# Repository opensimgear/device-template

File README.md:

# OpenSimGear device template

## Development status and disclaimer

This project is heavily under development and is not ready for use. Use it entirely at your own risk. To the fullest extent permitted by applicable law, the authors and contributors disclaim all liability for any damage, loss, or other issues arising from its use.

Start a new device with C firmware, electronics and mechanical designs in one repository. The **STM32G0B1CBT6 v0.1.0** starter provides **eight analogue inputs, 24 digital lines and optional 16-input I²C expansion boards**. A build-time profile supplies factory defaults; validated runtime configuration selects and calibrates the controls a particular device uses.

## What is implemented

- Configurable buttons, maintained contacts, analogue axes, eight-way hats, rotary encoders and three-position selectors. Unused controls are omitted from the HID descriptor and report.
- `example`, three-command `shifter`, `expanded`, single-button `master_caution` `radio_panel` and CDC-only `output_only` factory profiles; runtime drafts cover every control kind, channel mapping, axis calibration/inversion/deadzone, expansion masks and Unicode controller names. Validation rejects overlapping pins and oversized HID reports.
- One bounded configuration writer, explicit Apply/Save/discard/reset, a separate interrupted-write-safe settings journal, and direct USB descriptor replacement while detached. Cockpit accesses the same runtime core through the matching gateway; the independent JSON device simulation runs this C implementation.
- Optional 3.3 V TCA9555 input boards on I²C, with missing-board diagnostics and recovery that prevents held momentary contacts from generating a new press.
- Composite USB HID + CDC serial, unique serial number from the MCU's 96-bit UID.
- Serial `hello`, `info`, `inputs`, LED control and CAN status diagnostics.
- Device-advertised volatile actions with typed parameters, catalogue revisions and state readback. Cockpit controls the current board's monochrome status LED and the native simulator's RGB LED 1/boolean LED 2 through the same action registry and gateway route, including disabled HID controllers and direct USB ownership.
- Independent mapped-button/encoder transition capture with a 64-record volatile log, 16-record pages, held-state baselines and explicit stream/gap errors. Short debounced presses remain readable while HID is disabled or direct USB owns input. The Master Caution simulator uses the board LED action contract. Radio observations add maintained/selector metadata and independently calibrated axes with availability flags.
- Bounded character-display ports with declared columns, rows and ASCII/UTF-8 scalar-cell encoding, typed text setters and callback readback. The native radio supplies 7-cell frequency, 2-cell preset and 16-cell text ports through production firmware. The starter has no fitted display and advertises only its actual LED.
- Cyphal/CAN device with automatic node-ID selection, standard Heartbeat/GetInfo, profile discovery and input delivery through the STM32 gateway; direct USB ownership and completion-acknowledged encoder events.
- Shared profile validation, HID descriptor generation, debouncing, axis scaling, hat decoding, bounded encoder events, TCA9555 acquisition and line handling in [firmware-common](https://github.com/opensimgear/firmware-common), with pinned dependencies.
- KiCad schematic, exact-part BOM and local libraries, with separate four-layer production and two-layer Makera Z1 layouts. One current circuit is maintained at PCB version 0.1.0; [versions stay fixed until launch](electronics/VERSIONING.md).

**Status on 2026-10-14:** all six factory profiles cross-build and seventeen native suites pass with address/undefined-behavior sanitizers, including independent calibrated axes, bounded display callbacks, panel events, advertised actions, runtime configuration, actual dynamic USB descriptor callbacks, Unicode names, CAN delivery and interrupted settings/boot-journal writes. Cross-firmware tests connect actual acquisition/client code to the [device-gateway](https://github.com/opensimgear/device-gateway) discovery, registry and USB completion logic. Production schematic ERC, PCB DRC and schematic/PCB parity pass with zero violations or missing connections. These are software and CAD checks; no STM32 board has been physically validated. Runtime input configuration and saved calibration are implemented in portable code and the STM32 adapter. Gateway discovery now automatically enables new compatible identities in persistent descriptor order, with logical CAN routes 1–32. Explicitly disabled devices remain configurable without a gateway HID collection; re-enabling appends them. Matching gateway/device helpers are required for routes above ten. Implementation and qualification work is tracked in the [GitHub project](https://github.com/orgs/opensimgear/projects/2).

## Start here

- [Run native devices from JSON](simulation/README.md)
- [Firmware build, flash and console instructions](firmware/README.md)
- [CAN integration, ownership and firmware validation](firmware/CAN_BRINGUP.md)
- [Input examples, HID mapping and control wiring](firmware/profiles/README.md)
- [Starter board and pinout](electronics/boards/starter/0.1.0/README.md)
- [Optional 16-input expansion board wiring](electronics/expansion/tca9555/README.md)
- [Fabrication construction and home-milling plan](electronics/boards/starter/0.1.0/FABRICATION.md)
- [Validation record](electronics/boards/starter/0.1.0/VALIDATION.md)
- [Schematic PDF](electronics/boards/starter/0.1.0/review/schematic.pdf)
- [Front copper preview](electronics/boards/starter/0.1.0/review/pcb.svg)

## Run simulated devices

Start Cockpit normally and run the gateway from the [device-gateway simulation](https://github.com/opensimgear/device-gateway/tree/main/simulation). From this repository, start a separate terminal for each device:

```sh
python3 simulation/run.py --config simulation/configs/pedals.json
python3 simulation/run.py --config simulation/configs/button-panel.json
python3 simulation/run.py --config simulation/configs/shifter.json
python3 simulation/run.py --config simulation/configs/master-caution.json
python3 simulation/run.py --config simulation/configs/radio-panel.json
python3 simulation/run.py --config simulation/configs/output-only.json
```

Each JSON declares a unique identity, controller name and input arrays. `output-only.json` and `output-only-board-led.json` declare empty inputs with the same production RGB/boolean or fitted monochrome LED callbacks. They enroll without a HID controller and accept exclusive volatile endpoint leases with independent expiry/fallback. The gateway exposes the devices to Cockpit through its ordinary protocol. The first launch initializes pinned dependencies and builds into this repository’s `.simulation/`; saved configuration survives independent device, gateway and Cockpit restarts. See the [simulation guide](simulation/README.md) for JSON fields, input controls, state isolation and native tests.

Gateway and Cockpit E2E runners clone the components they require under their own `.e2e/` directories and initialize dependencies before building. This repository’s integration workflow checks out an immutable gateway runner commit with the same firmware-common pin, then supplies the current device source explicitly. Build commands do not invoke another repository’s E2E runner.

## Create a device

1. Select **Use this template** on GitHub. Replace the device overview and remove unused edition placeholders.
2. Keep common implementation in firmware-common; update its full commit pin deliberately.
3. Copy a firmware profile, assign its physical inputs and HID usages, and select it with `OSG_DEVICE_PROFILE`. The profile supplies factory defaults for USB descriptors, input reports and Cyphal capability announcements. Cockpit can configure the module through the matching gateway, including all input kinds and calibration; the module USB console also accepts `config <child-command>`. Explicit Apply detaches USB before publishing a changed descriptor, and Save persists settings. See the [runtime command contract](https://github.com/opensimgear/protocol/blob/main/serial/runtime-configuration.md).
4. Supply USB IDs you are authorized to use before flashing. No public OpenSimGear allocation is claimed.
5. Change the board target and electronics together, adapt the routing and complete the documented checks before fabrication.
6. Add mechanical designs under `hardware/variants/<edition>/<revision>` and maintain a compatibility table mapping mechanical revisions and PCB versions to compatible firmware targets.

## Layout

| Directory | Ownership |
| --- | --- |
| `simulation/` | Independent native device runtime, JSON examples, build/launch commands and tests |
| `firmware/` | Application, physical control profile, board target and build entry point |
| `electronics/boards/starter/0.1.0/` | Generic PCB/schematic, BOM, pinout and validation |
| `electronics/expansion/tca9555/` | Compatible optional input-board wiring and qualification contract |
| `hardware/variants/lite/` | Reserved Lite mechanical directory |
| `hardware/variants/pro/` | Reserved Pro mechanical directory |

Lite/Pro editions may share firmware and electronics. A material change alone does not require a new controller identity or copied firmware. Mechanical designs remain placeholders. Gateway electronics and firmware live in [device-gateway](https://github.com/opensimgear/device-gateway). Template updates do not automatically update repositories created from it.

## Licensing

Copyright © Ivan Gregurić Ortolan. All rights reserved for original OpenSimGear material while licensing is under review. The [temporary licensing policy](LICENSE) defines the current scope for firmware, electronics, mechanical designs and other original material. Creative external contributions are suspended during review; [CONTRIBUTING.md](CONTRIBUTING.md) explains the policy for factual bug reports and questions. Included KiCad library data retains its own [license](electronics/boards/starter/0.1.0/LICENSE-KICAD.md). Fetched firmware dependencies retain their upstream licenses; see [third-party notices](firmware/THIRD_PARTY.md).

## JLCPCB exports

From this repository root, run `sh tools/bundle-jlcpcb.sh` for the latest numeric board version, or `sh tools/bundle-jlcpcb.sh 0.1.0` for a specific version. Requires KiCad 10 (`kicad-cli`) and Python 3. The script generates a Gerber ZIP plus separate JLCPCB BOM/CPL CSVs in the workspace `.research/jlcpcb/` directory. Use `--output-dir path` to change the destination or `--smd-only` to omit through-hole assembly. See [tool usage](tools/README.md) and the board’s fabrication notes before ordering.

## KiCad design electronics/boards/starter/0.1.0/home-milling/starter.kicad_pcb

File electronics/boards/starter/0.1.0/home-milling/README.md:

# Home-milling device prototype

## Development status and disclaimer

This project is heavily under development and is not ready for use. Use it entirely at your own risk. To the fullest extent permitted by applicable law, the authors and contributors disclaim all liability for any damage, loss, or other issues arising from its use.

This is a separate two-layer bench layout of the canonical v0.1.0 circuit in the parent directory. It targets a Makera Z1 with the PCB toolkit and **unplated holes**. The additional area reserves accessible 1.80 mm wire lands for every MCU signal and the larger generic input banks. The assembled board is 105 × 125 mm; the routed blank is 110 × 125 mm including a removable 5 mm registration rail on its west side. USB and both powered-CAN sockets face the east edge. The nominal USB and RJ connector mouths align with the east PCB edge. Verify actual plug access, connector fit and strain clearance with purchased parts.

The layout keeps the original STM32G0B1CBT6 LQFP48, USB4105-GF-A, TCAN3413D and LM66100 component lands. Open signal runs use 0.30 mm tracks; local IC escapes, crowded routing lanes and USB use 0.20 mm. The final layout contains 4,586 mm of 0.30 mm copper and 1,395 mm of 0.20 mm copper; wider power routing is counted separately. Copper clearance is at least 0.20 mm. The editable stackup records two bare 35 µm copper faces and a nominal 1.53 mm FR4 core for a 1.60 mm laminate; actual copper/core thickness and dielectric properties must be measured or supplied by the laminate vendor. The nominal epsilon/loss values are metadata assumptions, not an impedance design. The 12 V pass-through is 1.00 mm. BUCK_5V uses 0.4002–0.50 mm, SYS_5V uses 0.20–0.50 mm including a short regulator escape, USB_VBUS uses 0.20–0.30 mm, and +3V3 uses 0.20–0.30 mm. Narrow pin transitions and the eventual measured power budget require populated-board checks. Dimensions describe nominal copper, not a verified machining result.

## Generic input connections

This layout implements the same eight analogue channels, 24 digital lines and local I²C expansion interface as the canonical board. Each device wires only the controls enabled by its firmware profile. Unused control connections are omitted from the advertised controller profile.

| Header | Pin assignment |
| --- | --- |
| J5, J7–J13 | Eight axes A0–A7; pin 1 +3V3, pin 2 signal, pin 3 GND |
| J14 | Pins 1–6 D0–D5; pin 7 GND |
| J15 | Pins 1–6 D6–D11; pin 7 GND |
| J16 | Pins 1–6 D12–D17; pin 7 GND |
| J17 | Pins 1–6 D18–D23; pin 7 GND |
| J18 | Pin 1 +3V3, pin 2 SDA, pin 3 SCL, pin 4 GND |

Axes use the canonical per-channel input resistor, filter capacitor and weak midpoint bias. Digital contact inputs have 10 kΩ pull-ups and are intended to close to GND. I²C is a short internal 3.3 V connection for optional 16-input boards, not an external cockpit bus. Do not apply 5 V or 12 V to analogue/digital inputs or use the USB/CAN supply pins as control inputs. See the [shared electrical design](../ELECTRICAL.md) and [pin allocation](../pin-allocation.json).

## Qualify the actual process first

Mill and populate the [qualification coupon](coupon/README.md) before this device. The USB and MCU footprints have 0.20 mm nominal gaps, leaving no process margin if the machine only just achieves that isolation. Test the cutter, board flatness, measured thickness, probing, opposite-face registration, isolation, pad adhesion and hand soldering with the actual laminate and purchased parts. Optional toolkit solder mask does not change the copper target or establish USB impedance.

The removable rail has two 2.00 mm NPTH registration holes, at board coordinates (77.5,64) and (77.5,181) mm. They are a layout starting point. Measure the actual fixture/dowel pins and adapt hole diameter and fit before generating CAM; the kit's pin diameter has not been established. Remove the rail at the user-drawing guide x=80 mm after both faces and drilling are complete. Mounting holes on the finished board remain separate.

## Unplated construction

Every electrical layer transition uses a **0.80 mm drilled hole with 1.80 mm copper lands**, joined by a wire soldered on both faces. These are represented by KiCad vias solely to model the completed hand-wired connection. The raw milled board has no conductive barrel. The [wire-join list](review/wire-joins.csv) records all **224** positions and nets. Complete and inspect every join before power-on. This assembled connectivity includes 1,701 copper track segments. The wire diameter and solder fillet must fit the 0.80 mm holes. Toolkit rivets are not assumed to fit: a rivet with 1.00 mm outside diameter does not fit this selected hole.

Long-leaded Evercom 5301-4P4C contacts, headers, buttons and the RECOM converter attach electrically on the **bottom face only**. Front track/zone keepouts around those component holes prevent a hidden need to solder under a connector or component body. Their front annuli are mechanically incidental and cannot bridge faces.

The USB4105 shell is different. Its nominal 0.95 mm stakes do not reach the back surface of 1.6 mm laminate. Solder its four shell lands from the **front**, making accessible fillets outside the case; the front shell ground must reach a verified ground wire join. Inspect fit, solder access and mechanical retention on the actual sample before committing a device. Back annuli do not turn short shell stakes into through leads. USB SMD contacts also solder on the front. C6–C9 (MCU decoupling) and C11 (USB power decoupling) are back-face SMD capacitors. C6–C9 sit directly beneath the MCU and connect to its accessible supply and ground wire joins; solder and inspect these back-face paths. Populate back-face parts only after both faces have been milled, drilled and inspected.

Retained drill/slot dimensions are distinct from the isolation cutter:

| Feature | Nominal hole/slot |
| --- | --- |
| Manual wire layer joins | 0.80 mm round |
| USB shell stakes | 0.60 × 1.70 and 0.60 × 1.40 mm slots |
| USB locating pegs | 0.65 mm round |
| Evercom 4P4C contacts / both locating pegs | 0.90 / 3.20 mm round |
| Samtec header leads | 1.02 mm round |
| Omron button leads | 1.10 mm round |
| RECOM converter leads | 1.00 mm round |
| Board mounting / rail registration | 3.20 / 2.00 mm round |

A 0.80 mm drill cannot produce the USB's 0.60 mm slots. Plan suitable small-slot tooling/CAM and inspect actual component fit. Do not enlarge connector slots or locating holes just to use one tool. Electrical holes here are unplated despite the canonical footprints' commercial plated-hole descriptions; the parent footprint/source review explains the nominal manufacturer geometry.

## Electrical and USB limits

This is a bench prototype, with a two-layer ground arrangement and manually soldered connections. It is **not** the 90 Ω controlled-impedance fabrication layout. USB leaves the MCU through accessible soldered-wire joins and continues on the back before returning to the front protection/connector routing. Neither this two-layer geometry, its extra wire transitions nor successful enumeration qualifies USB signal integrity; enumeration and signal quality require bench testing with the actual assembled prototype. Use the parent's JLCPCB four-layer layout and specified impedance process for that review.

The exact CAN jack is Evercom 5301-4P4C (LCSC C3097715), with an 11.10 × 18.05 × 11.45 mm body and a nose 14.25 mm from its footprint origin. Both 3.20 mm locating holes retain the independently checked drawing dimensions. Pin 1 is BUS_12V, pin 2 CAN_H, pin 3 CAN_L and pin 4 GND; both jacks are parallel connections to one linear bus.

The circuit and firmware pin mapping are shared with the canonical version: USB direct operation, two CAN pass-through connectors, 12 V alongside CAN, local protection/regulation and USB/bus power selection. The RJ sockets are powered CAN, not telephone or Ethernet ports. v0.1.0 firmware implements Cyphal/CAN discovery, gateway input delivery and direct USB ownership; see [CAN integration](../../../../../firmware/CAN_BRINGUP.md). Software tests and this PCB review do not establish physical hot-plug, ownership handover or USB/CAN behavior. Perform continuity, shorts, power-rail and supply handover checks before connecting a PC or CAN chain.

## Shared circuit and source refresh

Run `python3 regenerate_schematics.py` from this directory to regenerate both home schematic files from the parent v0.1.0 sources. The generator modifies only symbol Footprint properties using `source-footprints.json`; all references, part values, net names and circuit connectivity remain shared. HomeMilling footprint variants retain the exact component land/drill dimensions. The board arrangement and wire-via rules are specific to this prototype. The [parent purchasing BOM](../bom.csv) identifies the same components; its footprint column describes the production layout. Use the HomeMilling variants here for this board, rather than changing the purchasing parts.

Review exports and native KiCad reports are under `review/`: [schematic PDF](review/schematic.pdf), [two-face routing PDF](review/routing.pdf), [front copper](review/front.png), [back copper](review/back.png), [ERC](review/erc.rpt) and [DRC](review/drc.rpt). The final source has zero ERC violations, zero all-track DRC violations, zero unconnected items and zero schematic parity issues. A separate construction audit models the long-lead component pads as bottom-only and the four short USB shell lands as front-only; it retains the documented wire joins and also finds zero unconnected items. Its intentional diagnostic pad transformations produce expected library/pad-type warnings, not changes to the deliverable PCB. See the [unplated connectivity record](review/UNPLATED-CONNECTIVITY.md), [independent construction review](review/CONSTRUCTION-AUDIT.md) and `audit_unplated.py` for the precise checks. No CNC toolpaths or machine-ready milling files are supplied. CAM must be generated against the qualified machine, fixture, cutter and measured laminate.

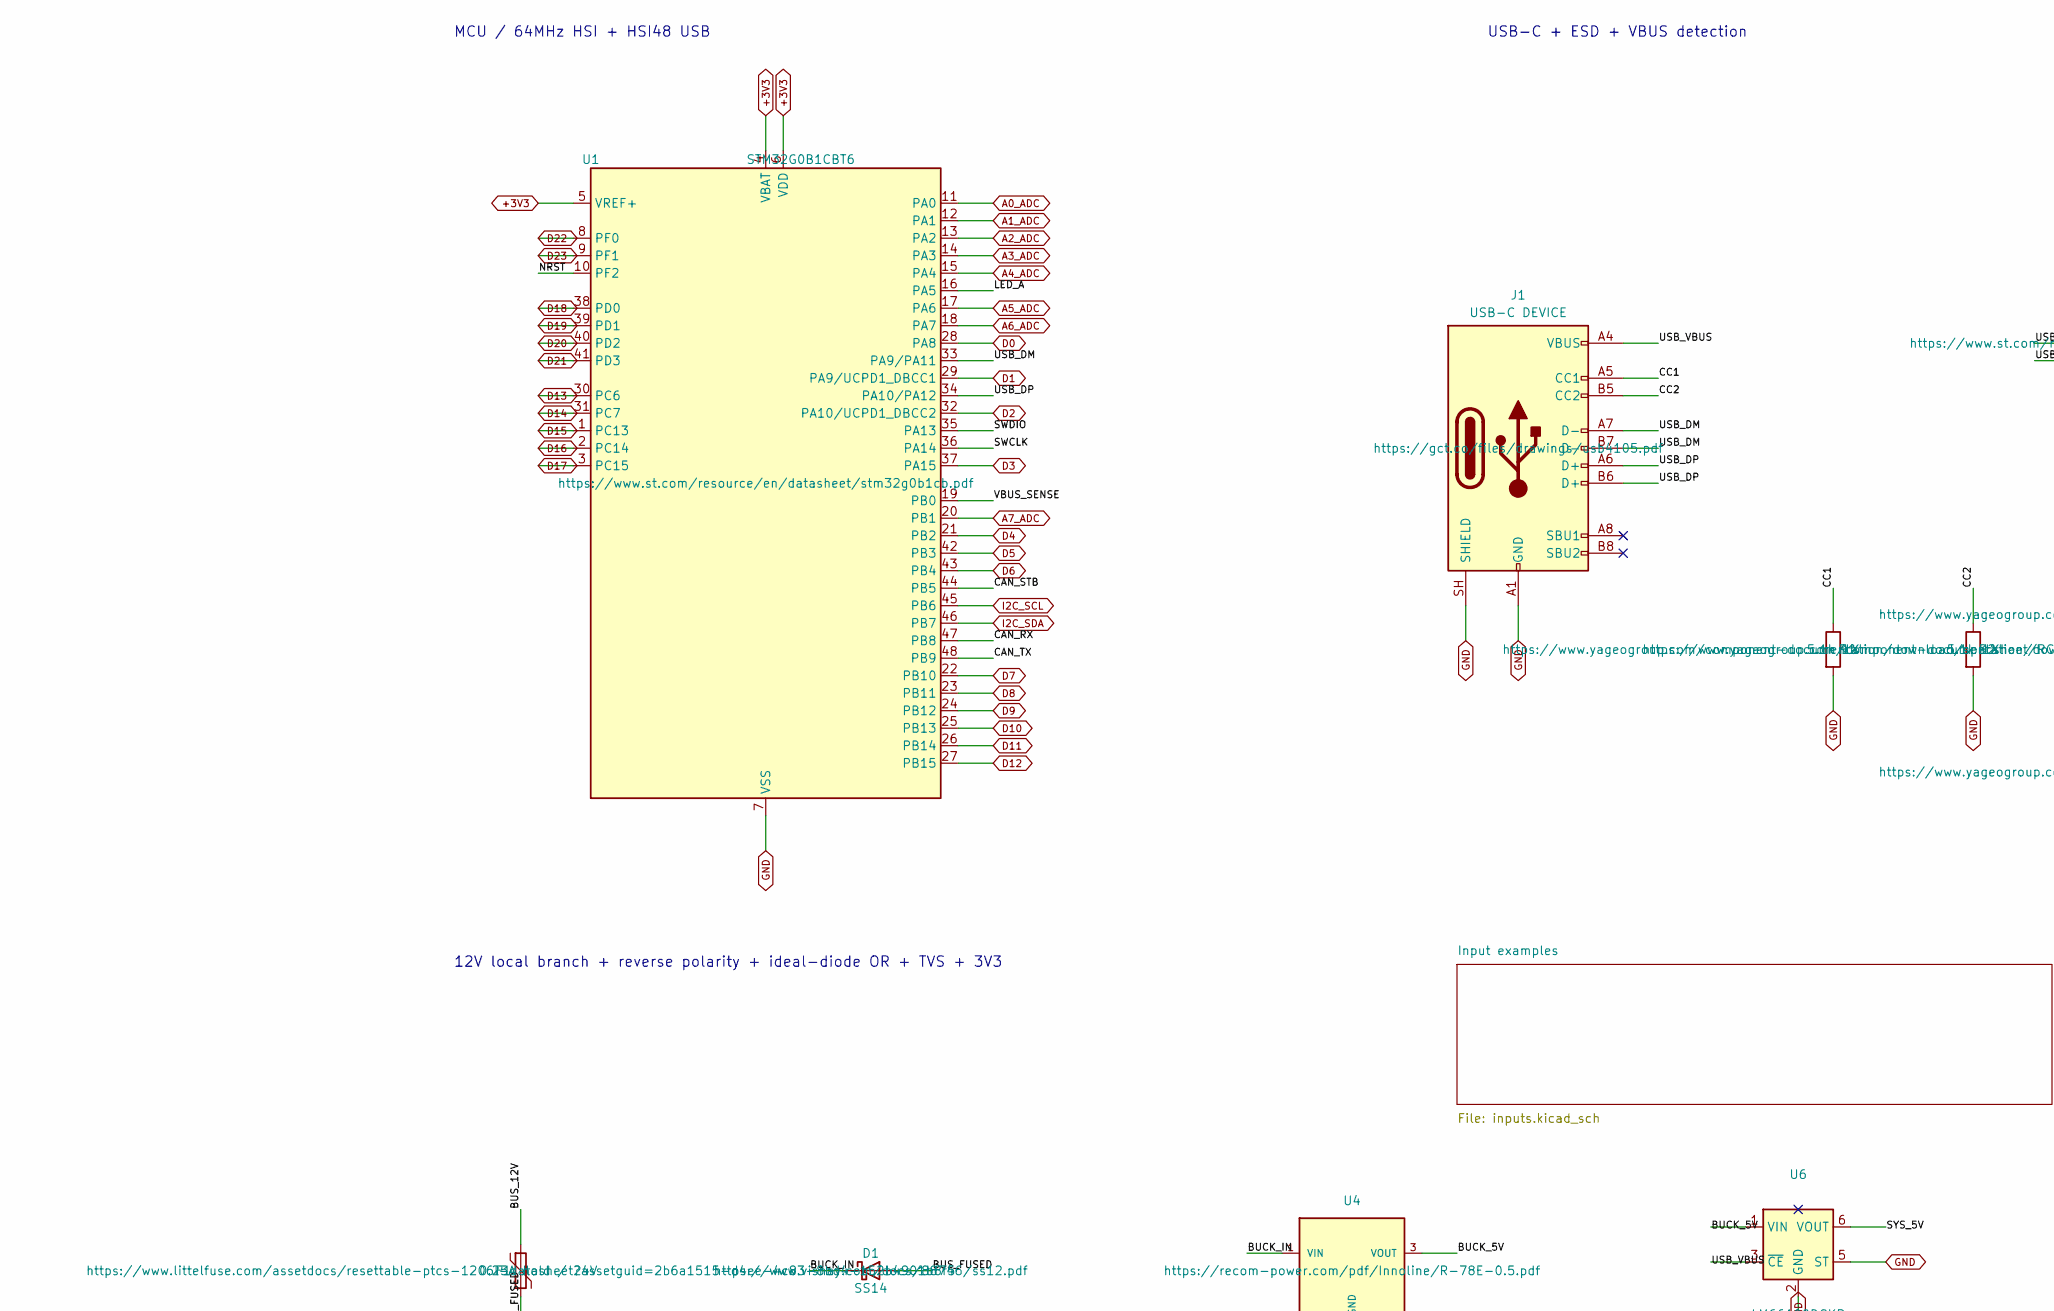
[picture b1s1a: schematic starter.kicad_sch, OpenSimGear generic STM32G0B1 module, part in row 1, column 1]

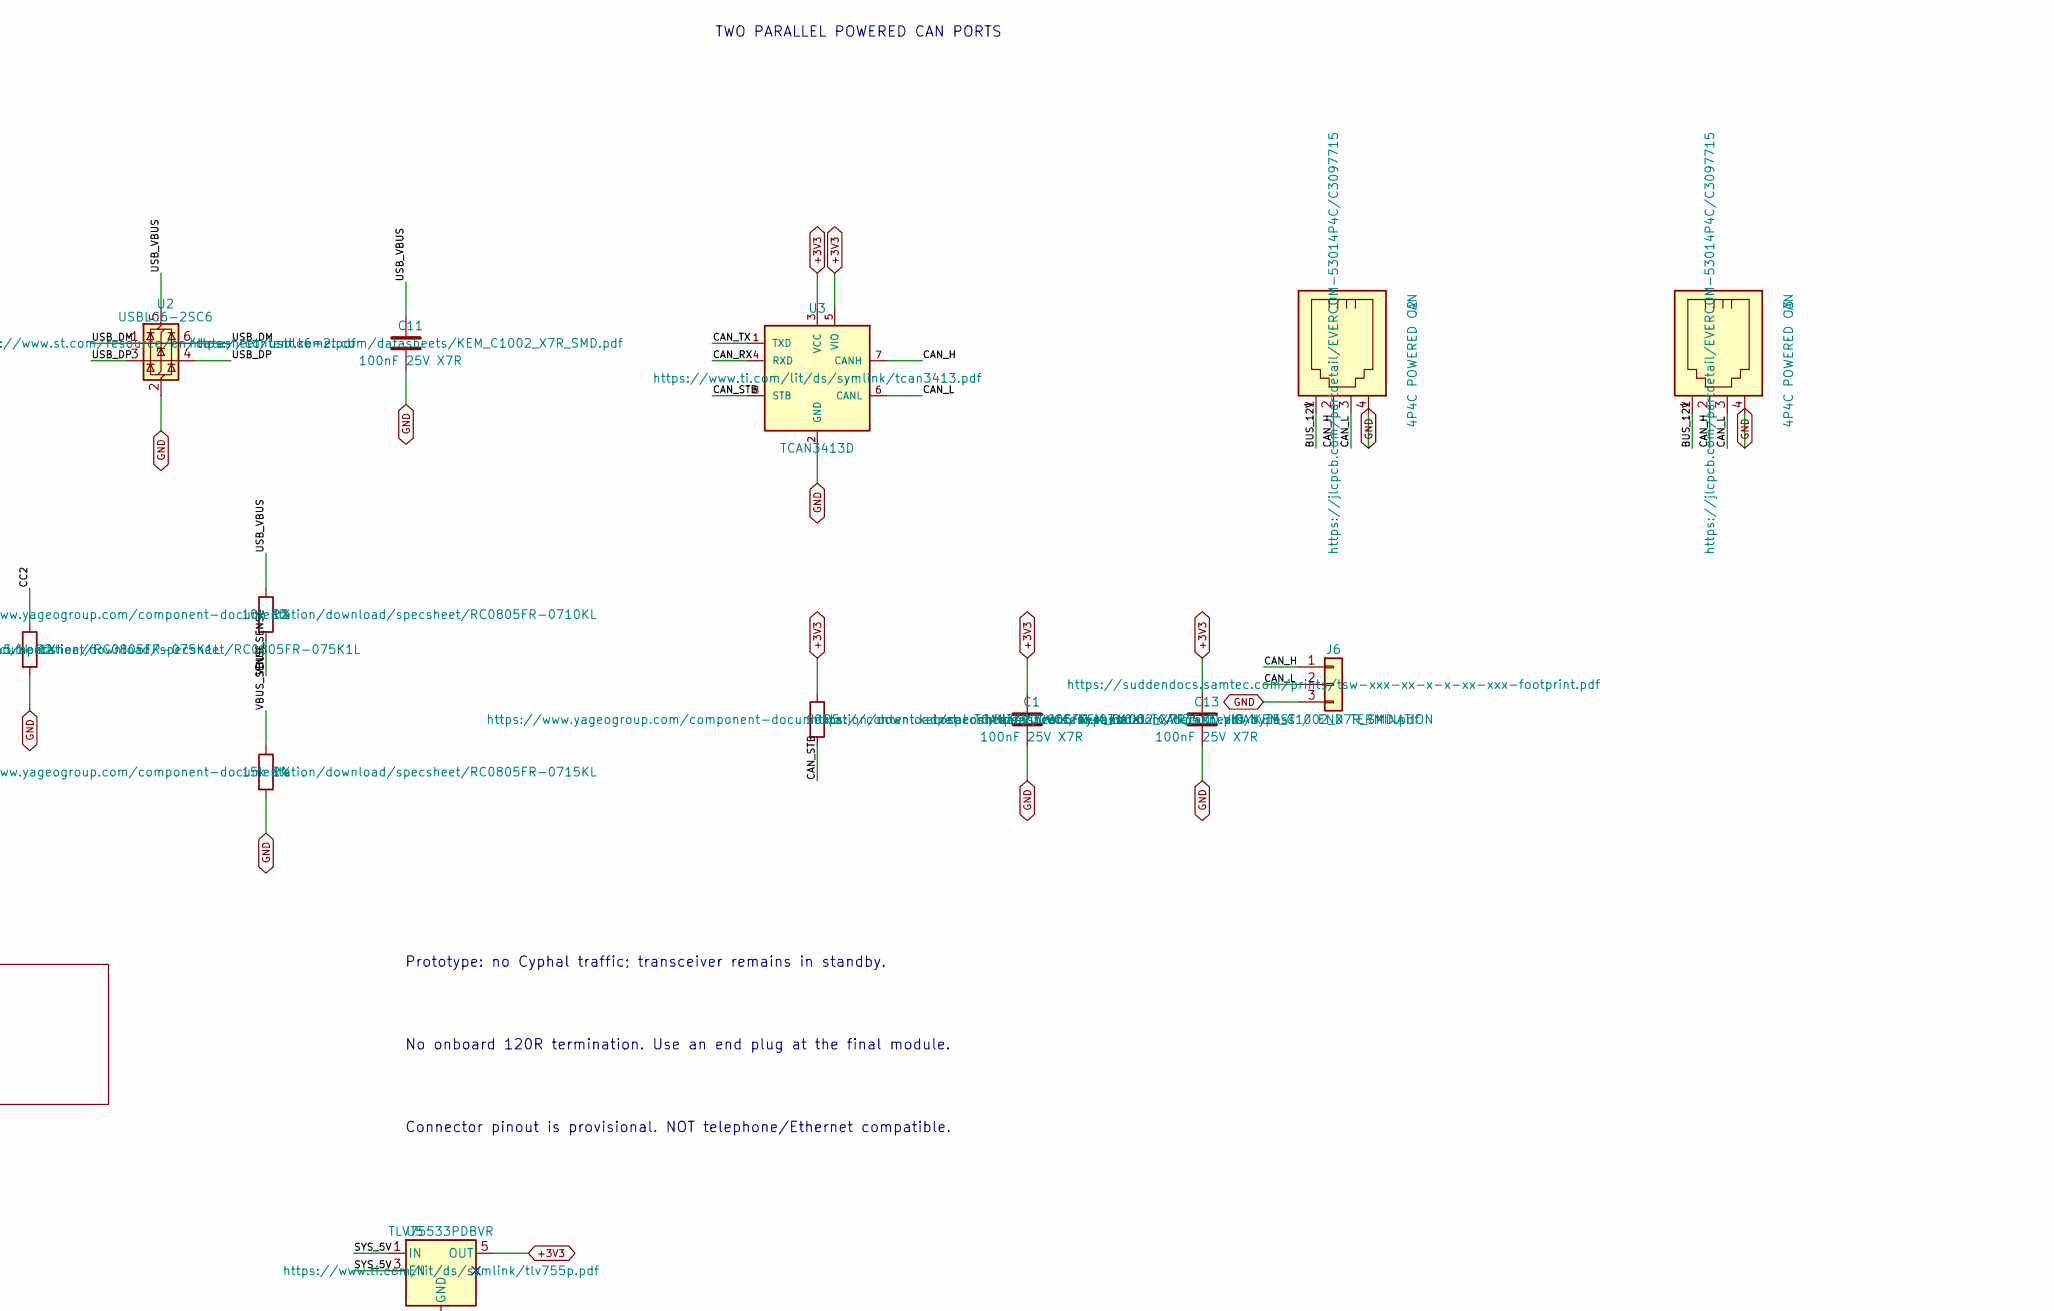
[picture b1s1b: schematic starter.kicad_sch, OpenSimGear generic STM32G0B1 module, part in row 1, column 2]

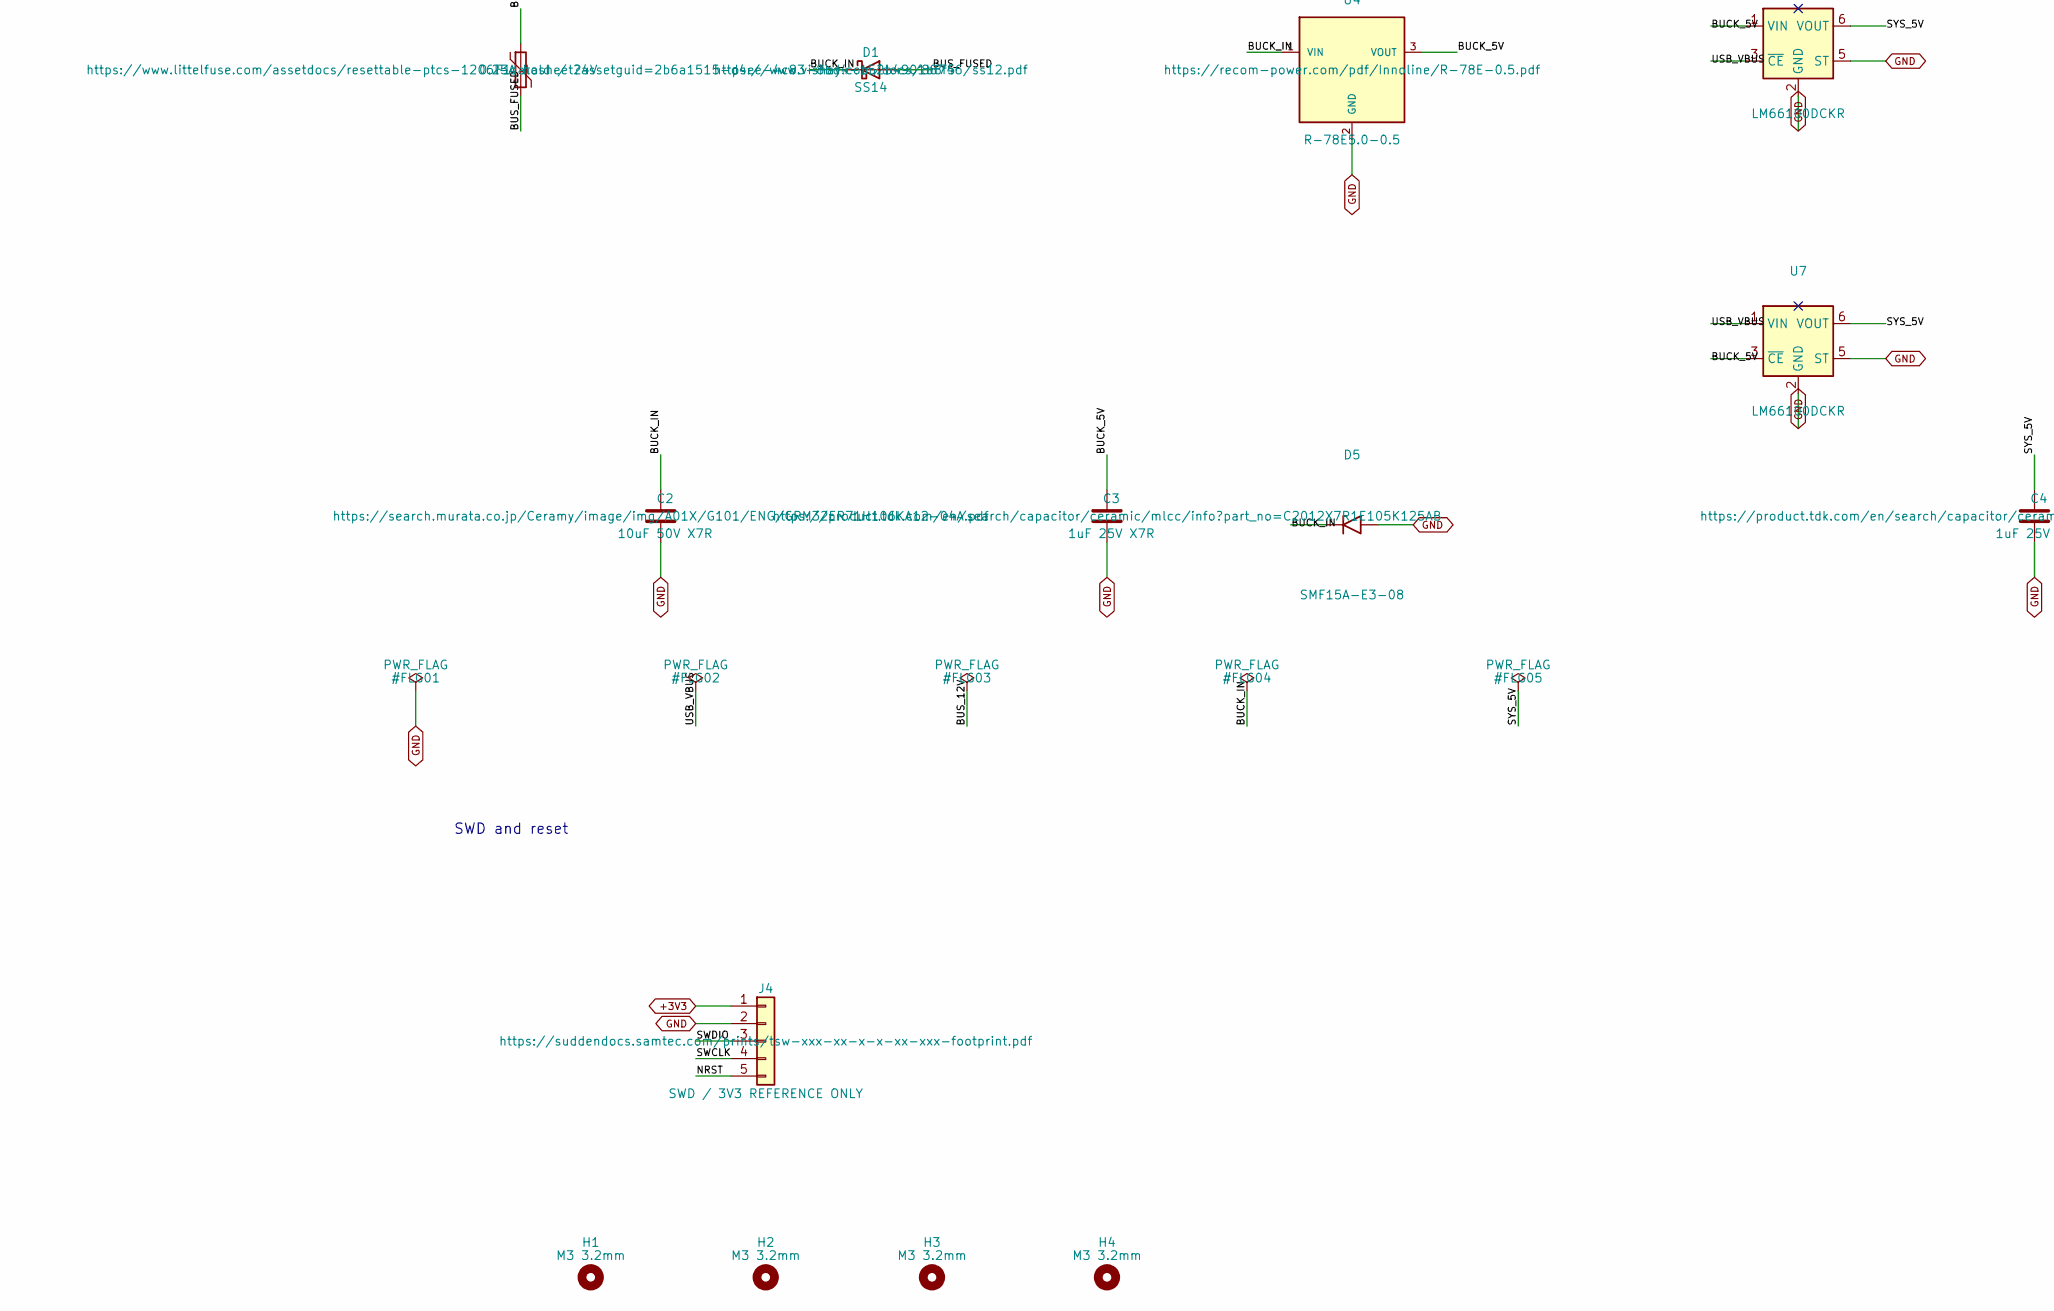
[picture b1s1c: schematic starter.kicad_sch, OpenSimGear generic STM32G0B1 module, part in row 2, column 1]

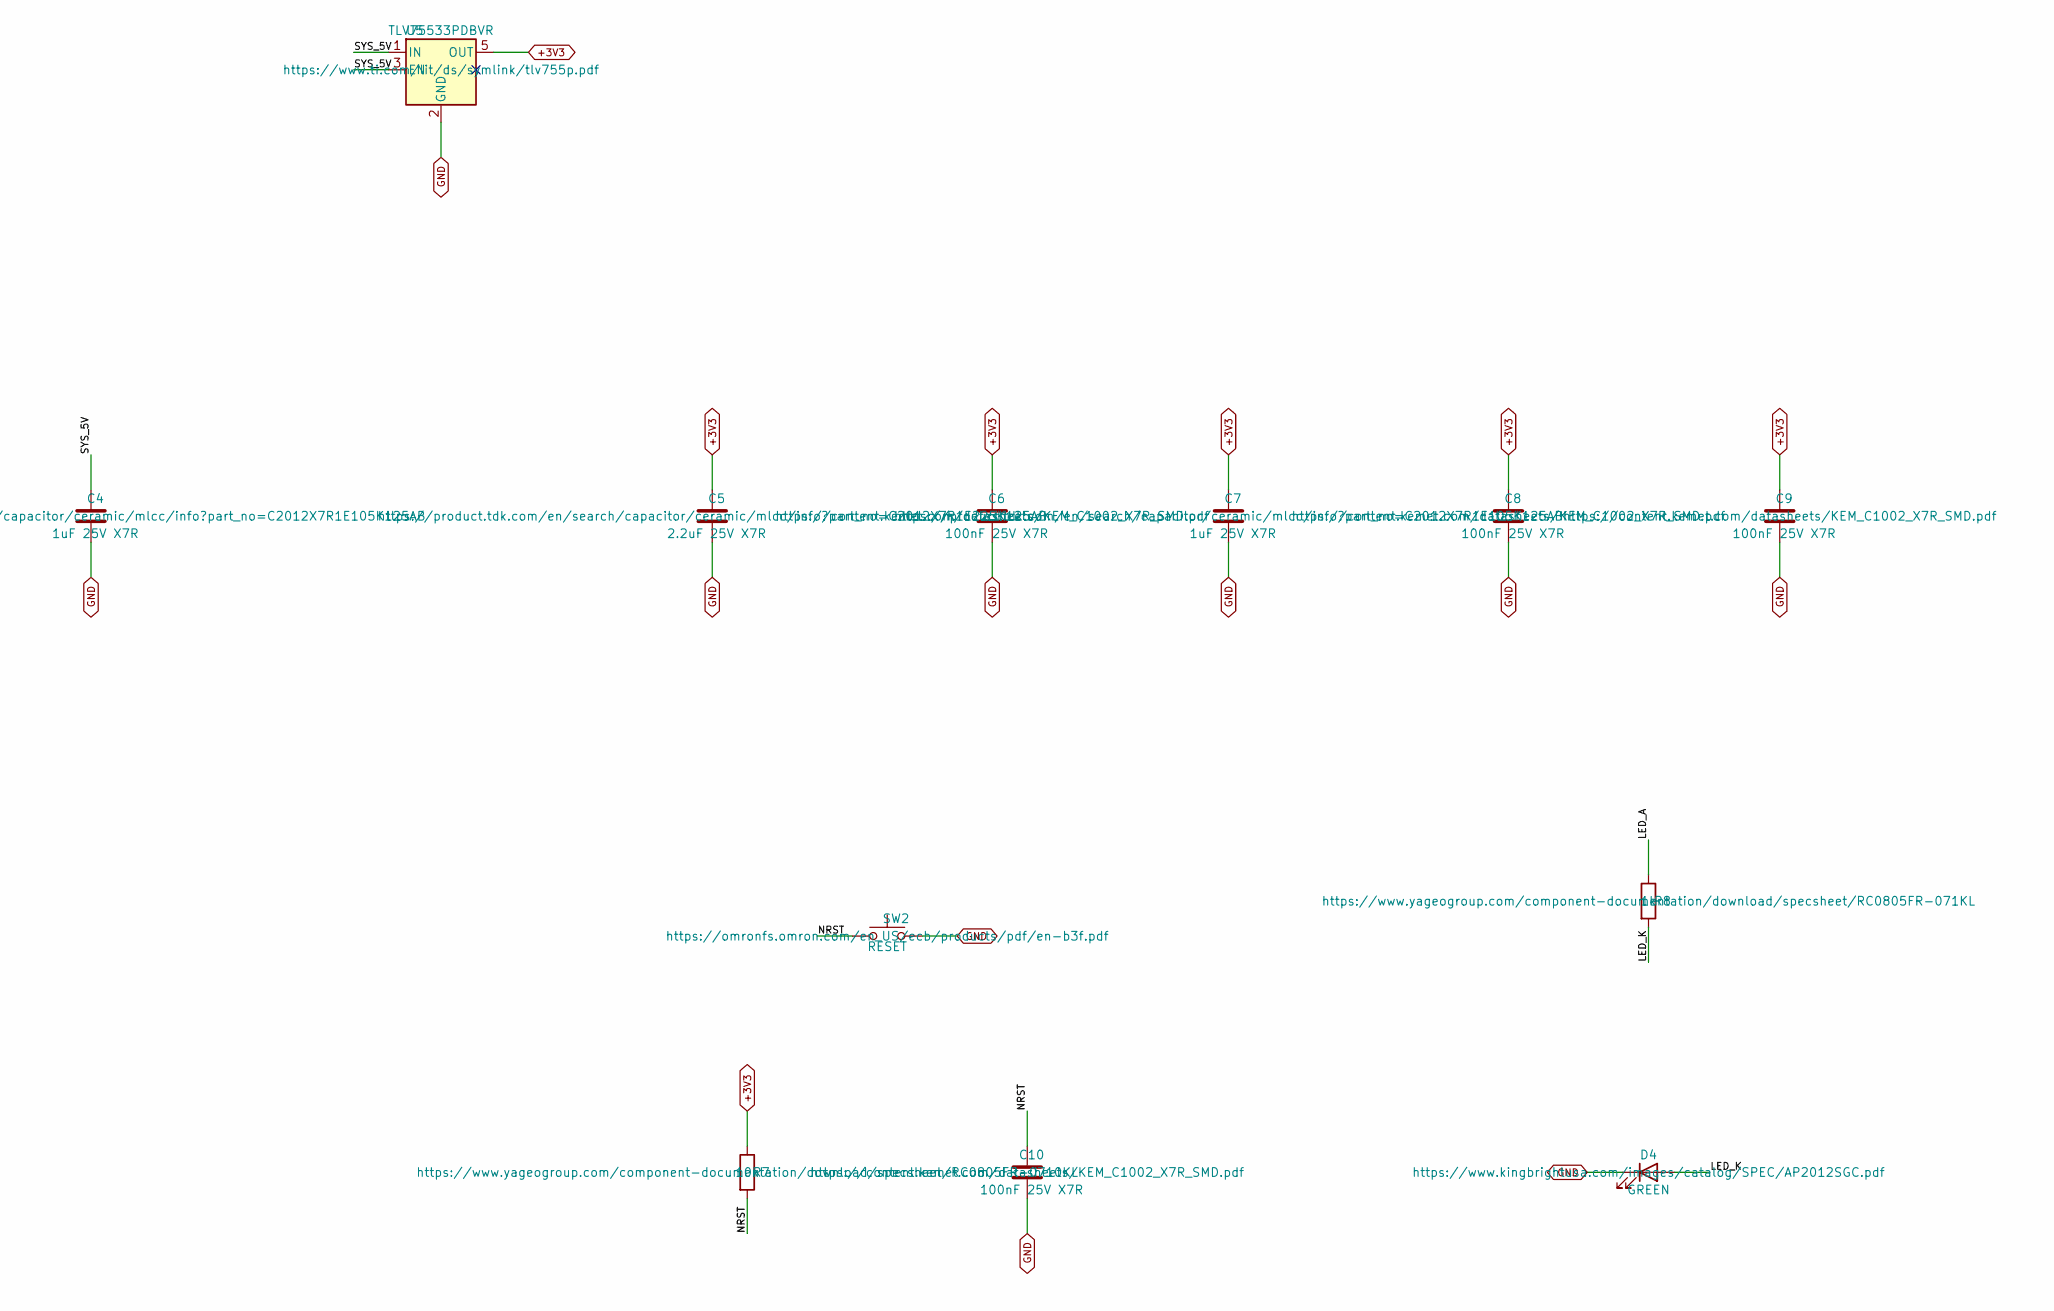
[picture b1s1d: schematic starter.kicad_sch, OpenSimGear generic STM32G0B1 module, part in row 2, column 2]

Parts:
C1: 100nF 25V X7R; C1_C_0805_2012Metric_HomeMilling; MPN C0805C104K3RACTU
C2: 10uF 50V X7R; C2_C_1210_3225Metric_HomeMilling; MPN GRM32ER71H106KA12L
C3: 1uF 25V X7R; C3_C_0805_2012Metric_HomeMilling; MPN C2012X7R1E105K125AB
C4: 1uF 25V X7R; C4_C_0805_2012Metric_HomeMilling; MPN C2012X7R1E105K125AB
C5: 2.2uF 25V X7R; C5_C_0805_2012Metric_HomeMilling; MPN C2012X7R1E225K125AB
C6: 100nF 25V X7R; C6_C_0805_2012Metric_HomeMilling; MPN C0805C104K3RACTU
C7: 1uF 25V X7R; C7_C_0805_2012Metric_HomeMilling; MPN C2012X7R1E105K125AB
C8: 100nF 25V X7R; C8_C_0805_2012Metric_HomeMilling; MPN C0805C104K3RACTU
C9: 100nF 25V X7R; C9_C_0805_2012Metric_HomeMilling; MPN C0805C104K3RACTU
C10: 100nF 25V X7R; C10_C_0805_2012Metric_HomeMilling; MPN C0805C104K3RACTU
C11: 100nF 25V X7R; C11_C_0805_2012Metric_HomeMilling; MPN C0805C104K3RACTU
C13: 100nF 25V X7R; C13_C_0805_2012Metric_HomeMilling; MPN C0805C104K3RACTU
D1: SS14; D1_D_SMA_HomeMilling; MPN SS14-E3/61T
D4: GREEN; D4_LED_Kingbright_AP2012SGC_0805_HomeMilling; MPN AP2012SGC
D5: SMF15A-E3-08; D5_D_SMF_HomeMilling; MPN SMF15A-E3-08
F1: 0.25A hold / 24V; F1_Fuse_Littelfuse_1206L025-24YR_HomeMilling; MPN 1206L025/24YR
H1: M3 3.2mm; H1_MountingHole_3.2mm_M3_HomeMilling
H2: M3 3.2mm; H2_MountingHole_3.2mm_M3_HomeMilling
H3: M3 3.2mm; H3_MountingHole_3.2mm_M3_HomeMilling
H4: M3 3.2mm; H4_MountingHole_3.2mm_M3_HomeMilling
J1: USB-C DEVICE; J1_USB_C_Receptacle_GCT_USB4105-xx-A_16P_TopMnt_Horizontal_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; MPN USB4105-GF-A
J2: 4P4C POWERED CAN; J2_RJ4P4C_Evercom_5301-4P4C_Horizontal_HomeMilling; MPN 5301-4P4C
J3: 4P4C POWERED CAN; J3_RJ4P4C_Evercom_5301-4P4C_Horizontal_HomeMilling; MPN 5301-4P4C
J4: SWD / 3V3 REFERENCE ONLY; J4_PinHeader_Samtec_TSW-105-07-L-S_P2.54mm_Vertical_HomeMil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; MPN TSW-105-07-L-S
J6: CAN TEST / END TERMINATION; J6_PinHeader_Samtec_TSW-103-07-L-S_P2.54mm_Vertical_HomeMil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; MPN TSW-103-07-L-S
R1: 5.1k 1%; R1_R_0805_2012Metric_HomeMilling; MPN RC0805FR-075K1L
R2: 5.1k 1%; R2_R_0805_2012Metric_HomeMilling; MPN RC0805FR-075K1L
R3: 10k 1%; R3_R_0805_2012Metric_HomeMilling; MPN RC0805FR-0710KL
R4: 15k 1%; R4_R_0805_2012Metric_HomeMilling; MPN RC0805FR-0715KL
R5: 10k; R5_R_0805_2012Metric_HomeMilling; MPN RC0805FR-0710KL
R7: 10k; R7_R_0805_2012Metric_HomeMilling; MPN RC0805FR-0710KL
R8: 1k; R8_R_0805_2012Metric_HomeMilling; MPN RC0805FR-071KL
SW2: RESET; SW2_SW_PUSH_6mm_H4.3mm_HomeMilling; MPN B3F-1002-G
U1: STM32G0B1CBT6; U1_LQFP-48_7x7mm_P0.5mm_HomeMilling; MPN STM32G0B1CBT6
U2: USBLC6-2SC6; U2_SOT-23-6_HomeMilling; MPN USBLC6-2SC6
U3: TCAN3413D; U3_SOIC-8_3.9x4.9mm_P1.27mm_HomeMilling; MPN TCAN3413D
U4: R-78E5.0-0.5; U4_Converter_DCDC_RECOM_R-78E-0.5_THT_HomeMilling; MPN R-78E5.0-0.5
U5: TLV75533PDBVR; U5_SOT-23-5_HomeMilling; MPN TLV75533PDBVR
U6: LM66100DCKR; U6_TI_DCK0006A_SC70-6_LM66100_HomeMilling; MPN LM66100DCKR
U7: LM66100DCKR; U7_TI_DCK0006A_SC70-6_LM66100_HomeMilling; MPN LM66100DCKR

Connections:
+3V3: C1.1, C5.1, C6.1, C7.1, C8.1, C9.1, C13.1, J4.1, R5.1, R7.1, U1.4 (VBAT), U1.5 (VREF+), U1.6 (VDD), U3.3 (VCC), U3.5 (VIO), U5.5 (OUT); also elsewhere on the board
/BUCK_5V: C3.1, U4.3 (VOUT), U6.1 (VIN), U7.3 (~CE)
/BUCK_IN: C2.1, D1.1 (K), D5.1 (A1), U4.1 (VIN)
/BUS_12V: F1.1, J2.1, J3.1
/BUS_FUSED: D1.2 (A), F1.2
/CAN_H: J2.2, J3.2, J6.1, U3.7 (CANH)
/CAN_L: J2.3, J3.3, J6.2, U3.6 (CANL)
/CAN_RX: U1.47 (PB8), U3.4 (RXD)
/CAN_STB: R5.2, U1.44 (PB5), U3.8 (STB)
/CAN_TX: U1.48 (PB9), U3.1 (TXD)
/CC1: J1.A5 (CC1), R1.1
/CC2: J1.B5 (CC2), R2.1
/LED_A: R8.1, U1.16 (PA5)
/LED_K: D4.2 (A), R8.2
/NRST: C10.1, J4.5, R7.2, SW2.1, U1.10 (PF2)
/SWCLK: J4.4, U1.36 (PA14)
/SWDIO: J4.3, U1.35 (PA13)
/SYS_5V: C4.1, U5.1 (IN), U5.3 (EN), U6.6 (VOUT), U7.6 (VOUT)
/USB_DM: J1.A7 (D-), J1.B7 (D-), U1.33 (PA9/PA11), U2.1 (I/O1), U2.6 (I/O1)
/USB_DP: J1.A6 (D+), J1.B6 (D+), U1.34 (PA10/PA12), U2.3 (I/O2), U2.4 (I/O2)
/USB_VBUS: C11.1, J1.A4 (VBUS), J1.A9 (VBUS), J1.B4 (VBUS), J1.B9 (VBUS), R3.1, U2.5 (VBUS), U6.3 (~CE), U7.1 (VIN)
/VBUS_SENSE: R3.2, R4.1, U1.19 (PB0)
A0_ADC: U1.11 (PA0); also elsewhere on the board
A1_ADC: U1.12 (PA1); also elsewhere on the board
A2_ADC: U1.13 (PA2); also elsewhere on the board
A3_ADC: U1.14 (PA3); also elsewhere on the board
A4_ADC: U1.15 (PA4); also elsewhere on the board
A5_ADC: U1.17 (PA6); also elsewhere on the board
A6_ADC: U1.18 (PA7); also elsewhere on the board
A7_ADC: U1.20 (PB1); also elsewhere on the board
D0: U1.28 (PA8); also elsewhere on the board
D1: U1.29 (PA9/UCPD1_DBCC1); also elsewhere on the board
D2: U1.32 (PA10/UCPD1_DBCC2); also elsewhere on the board
D3: U1.37 (PA15); also elsewhere on the board
D4: U1.21 (PB2); also elsewhere on the board
D5: U1.42 (PB3); also elsewhere on the board
D6: U1.43 (PB4); also elsewhere on the board
D7: U1.22 (PB10); also elsewhere on the board
D8: U1.23 (PB11); also elsewhere on the board
D9: U1.24 (PB12); also elsewhere on the board
D10: U1.25 (PB13); also elsewhere on the board
D11: U1.26 (PB14); also elsewhere on the board
D12: U1.27 (PB15); also elsewhere on the board
D13: U1.30 (PC6); also elsewhere on the board
D14: U1.31 (PC7); also elsewhere on the board
D15: U1.1 (PC13); also elsewhere on the board
D16: U1.2 (PC14); also elsewhere on the board
D17: U1.3 (PC15); also elsewhere on the board
D18: U1.38 (PD0); also elsewhere on the board
D19: U1.39 (PD1); also elsewhere on the board
D20: U1.40 (PD2); also elsewhere on the board
D21: U1.41 (PD3); also elsewhere on the board
D22: U1.8 (PF0); also elsewhere on the board
D23: U1.9 (PF1); also elsewhere on the board
GND: C1.2, C2.2, C3.2, C4.2, C5.2, C6.2, C7.2, C8.2, C9.2, C10.2, C11.2, C13.2, D4.1 (K), D5.2 (A2), J1.A1 (GND), J1.A12 (GND), J1.B1 (GND), J1.B12 (GND), J1.SH (SHIELD), J2.4, J3.4, J4.2, J6.3, R1.2, R2.2, R4.2, SW2.2, U1.7 (VSS), U2.2 (GND), U3.2 (GND), U4.2 (GND), U5.2 (GND), U6.2 (GND), U6.5 (ST), U7.2 (GND), U7.5 (ST); also elsewhere on the board
I2C_SCL: U1.45 (PB6); also elsewhere on the board
I2C_SDA: U1.46 (PB7); also elsewhere on the board

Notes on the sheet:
MCU / 64MHz HSI + HSI48 USB
USB-C + ESD + VBUS detection
TWO PARALLEL POWERED CAN PORTS
12V local branch + reverse polarity + ideal-diode OR + TVS + 3V3
SWD and reset
Prototype: no Cyphal traffic; transceiver remains in standby.
No onboard 120R termination. Use an end plug at the final module.
Connector pinout is provisional. NOT telephone/Ethernet compatible.
